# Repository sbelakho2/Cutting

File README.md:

# STARZ Electronics · precision wire cutting and stripping

## Current work: S1-B — fabrication-ready design package (internal build)

**Start building now:** [fabrication guide](docs/31-fabrication-guide.md) —
ordered procurement, machining, assembly, energisation and first-article
steps with every check named. Evidence rules and warnings:
[master plan](docs/24-production-and-release-plan.md). One-page buying list
with every verified price and clickable source:
[sourcing list](docs/32-sourcing-list.md).

- [Selected cutting-axis hardware and scope](engineering/README.md)
- [Manufacturer drawings, actual ratings and rejected mismatches](engineering/sources/catalogue-evidence.md)
- [Shared mechanical/control definition](shared/cutting_head_spec.hpp)
- [Selected-head 3D assembly](engineering/generated/head/head-assembly.step)
- [Part manifest](engineering/generated/head/manifest.csv) and [CAD validation scope](engineering/generated/head/status.json)
- [Dimensioned R6 adapter A3 PDF](engineering/generated/drawings/H003-R6-adapter.pdf) and [browser drawing review](engineering/generated/drawings/index.html)
- [F101 R6 shaft A3 dimension sheet](engineering/generated/drawings/F101-R6-shaft.pdf), [machining-detail sheet](engineering/generated/drawings/F101-R6-details.pdf) and [shaft drawing review](engineering/generated/drawings/shaft-review.html)
- [F101 selected tapping tool and physical-tip setup](docs/14-f101-tapping-operation.md), [fabrication-tooling BOM](bom/fabrication-tooling.csv) and [blank shaft inspection record](docs/inspection/F101-R6.csv)
- [M201 measuring-encoder plate A3 drawing](engineering/generated/drawings/M201-R2-encoder-plate.pdf), [five-part encoder mount STEP](engineering/generated/measurement/encoder-mount.step) and [measurement assembly/calibration record](docs/13-measuring-interfaces-and-calibration.md)
- [P002 payoff spindle A3 drawing](engineering/generated/drawings/P002-R2-payoff-spindle.pdf), [P004–P007 payoff plates A3 drawing](engineering/generated/drawings/P004-P007-R2-payoff-plates.pdf) and [G101–G106 guard panels A3 drawing](engineering/generated/drawings/G101-G106-R2-guard-panels.pdf) with browser reviews (`payoff-spindle-review.html`, `payoff-plates-review.html`, `guard-panels-review.html` in the same directory)
- [Feed cartridge STEP](engineering/generated/feed/feed-cartridge.step), [four-roller layout STEP](engineering/generated/feed-cassette/feed-cassette.step), [machining and assembly record](docs/12-feed-cartridge-fabrication.md), [shaft/belt calculations](engineering/generated/feed-analysis/report.md)
- [Combined head/eight-roller placement STEP](engineering/generated/layout/head-and-feed-layout.step) and [cross-subsystem verification](engineering/generated/layout/status.json)
- [507-occurrence R3 full-machine STEP](engineering/generated/mechanism/full-machine.step) with pressure carriers, wire guides, measuring module, bed, welded frame, R2 guard selections and R2 payoff (spool, spindle, 6204 pockets, brake disc/caliper); [manifest](engineering/generated/mechanism/manifest.csv), [mechanism BOM](engineering/generated/mechanism/mechanism-bom.csv), [scope](engineering/generated/mechanism/status.json); [selected hardware](bom/selected-mechanism.csv) and [custom parts](bom/mechanism-custom-parts.csv)
- [Precision finishing cards](docs/21-precision-finishing.md): per-shaft matched j5 seat grinding and housing fine-boring cards from measured bearing bores
- [Physical qualification procedure and tool](docs/20-physical-qualification.md): ±(0.05 % + 0.20 mm) length cells, nip/wheel force windows, Cpk ≥ 1.33, fail-closed
- [Matched j5/C3 bearing fit](engineering/generated/bearing-fit/report.md) and [shaft matching limits](engineering/generated/bearing-fit/matching-limits.csv)
- [Feed R6 machined-section stiffness audit](engineering/generated/feed-sections/report.md):191 nominal B-rep sections, including the new chamfers and washer/key blends
- [Feed-shaft four-mesh 3D stress study](engineering/generated/feed-fem/report.md) and [model equations](docs/15-feed-shaft-stress-model.md); [torus-root rerun](docs/26-feed-shaft-torus-root-rerun.md); [regional submodel study](docs/28-feed-shaft-submodel-record.md)
- [Earlier focused full-shaft refinements](docs/16-local-shaft-refinement.md): six feature families,26 meshes,three background checks and52 audited fields
- [Earlier CAD-feature refinement and peak audit](docs/17-cad-feature-shaft-refinement.md)
- [Current A12 boundary-topology and stress investigation](docs/18-a12-boundary-topology.md)
- [Exterior-centroid diagnosis and torus-focused resolution](docs/19-exterior-centroid-diagnosis.md)
- [Current design basis and process geometry](docs/01-design-basis.md)
- [Current analytic-only report](engineering/generated/current-analytical/report.md) and [current numerical checks](engineering/generated/current-analytical/checks.csv); [archived R4 full FEM report](engineering/generated/analysis/report.md) and [historical sensitivity studies](engineering/generated/analysis/sensitivity.csv)
- [Adapter FEM with the preloaded elastic-foundation support](engineering/generated/adapter-r6-analysis/report.md)
- [Measuring-wheel calculation and calibration report](engineering/generated/measurement-analysis/report.md)
- [Production controller source](software/machine/): host-testable sequencing core, Pico 2/RP2350 target source and USB commissioning CLI
- [Legacy reference controls](software/firmware/firmware_controller.cpp): retained fault-injection model; does not operate hardware
- [IF-B01 placed/routed draft and manufacturing outputs](hardware/if-b01/README.md)
- [Cabinet controls and wiring design input](docs/22-controls-and-wiring.md)
- [Preliminary guard/payoff CAD accommodation](docs/25-preliminary-guard-and-payoff.md)
- [Guard/payoff R2 selection record](docs/26-guard-and-payoff-selection.md)
- [Machine assembly sequence and interface-fit register](docs/30-machine-assembly-sequence.md)
- [Physical contradiction audit](docs/28-physical-contradiction-audit.md)
- [Gate ledger — every open gate, category and closure action](docs/33-gate-ledger.md)
- [Purchase enquiries — ready-to-send letters for every external line](docs/35-purchase-enquiries.md)
- [Commissioning runbook — 11 phases, 69 steps closing every physical gate](docs/36-commissioning-runbook.md)
- [Weld and assembly procedures (payoff and guard)](docs/34-weld-and-assembly-procedures.md)
- [Master production and release plan](docs/24-production-and-release-plan.md): stepwise procurement, fabrication, assembly, inspection, commissioning and first-article gates; templates remain blank until actual work is performed.
- [Auditable sourcing evidence](bom/sourcing-evidence.csv): direct public-page observations and exact-SKU comparison boundaries; no delivered-cost claim without equivalent quotations. Added 2026-09-13: LC1D12BD EUR70.40 (Automation24), SKF bearing/retention GBP prices (Simply Bearings), with FAG/KOYO quality-equivalent comparisons in [catalogue evidence](engineering/sources/catalogue-evidence.md).
- [IF-B01/RP2350 GPIO allocation](hardware/if-b01/if-b01-gpio-allocation.csv): machine-readable connector-to-firmware allocation checked against the native intent, cabinet schedule and RP2350 source.

The new cutting head uses two complete HIWIN KK8610C-340A1-F0 axes (C-grade substitution, priced on the MISUMI VN shelf 2026-09-16) with real10mm lead, two34E1K-85/CL86T-V41 motor/driver kits and R+W MK2/100/50/8/14 couplings. The motors use original supplier STEP geometry, including cables and connectors, with the supplied removable shaft key removed for the keyless hub. Other purchased head components use catalogue-interface geometry.

The measuring-wheel source audit corrected the free circumference tolerance to **100±0.1 mm** and the uncalibrated1m allocation sum to **1.65 mm**, above the0.70 mm target. The new C++ phase-map fitter checks signed counts, reversals, observable data and independent validation residuals; its example data are **synthetic**, not measured calibration. The encoder tip is20 mm from its mounting face. The full-machine source includes the measuring shaft, pressure carriers and wire guides; each remains unbuilt and unqualified. The287-part combined head/feed layout is unchanged.

## Reproducibility

C++20; CMake/Ninja; OpenCASCADE7.9.3; Eigen; Gmsh; SuiteSparse/CHOLMOD with METIS. The `engineering` CMake preset builds the current head and numerical verification. The `engineering_generate` build target writes CAD/readback artifacts and engineering reports. The root `core` and `sanitize` presets build/test the host-side machine core and retained legacy reference code; `sanitize` enables AddressSanitizer and UndefinedBehaviorSanitizer. Root CTest also executes Python source-record validators for production evidence, IF-B01/RP2350 allocation and published mechanism artifacts; the C++ replacement engineering suite itself has no Python runtime dependency. When a compiler or cache option changes, configure with `cmake --fresh --preset <name>` so preset values are fully reapplied. The separate Pico SDK project under `software/machine/rp2350` builds target UF2 images. No build is physical qualification or permission to energise equipment.

The current **head R6 / feed R6 / measuring R1 / mechanism R3** source state extends the prior 492-part R1 mechanism to 507 source occurrences: eight R2-selected guard/actuator solids and seven R2 payoff solids (welded spool, Ø20 spindle, two 6204-pocket posts, base, brake disc, caliper bracket). Its mechanism test set covers the two wire diameters, STEP export/readback and four rejection cases (shifted bushing, slack carrier spring, light wheel and blocked guard wire route). Historical verification records for the earlier source states (64/64, 52/52, 54/54 native and ASan/UBSan runs, A12 topology, exterior-centroid diagnosis) are preserved in [docs/verification/](docs/verification/). The torus-root rerun ([record](docs/26-feed-shaft-torus-root-rerun.md)) and the [regional submodel study](docs/28-feed-shaft-submodel-record.md) close the feed-shaft regional gates; the adapter FEM now uses a preloaded Winkler elastic-foundation support ([report](engineering/generated/adapter-r6-analysis/report.md)). **The engineering suite is 83/83 native tests passing in 1847.54 s** at this source state; the core and sanitize presets pass 18/18 each.

Head:55 occurrences; cartridge32; four-roller layout116; combined head/eight-roller placement287; separate encoder face mount8. Head/feed moving parts retain17.5 mm X separation for all independent jawY positions. Feed report:25 checks,0 failures; nominal machined-section audit:191 sections,0 sampled stiffness failures. Bearing fit:256 corners,minimum1.28 µm residual clearance **conditional on its declared thermal envelope**,not a measured temperature prediction. Measurement report:392 synthetic held-out observations,0 residual failures; factory accuracy and the626 CN thermal screen remain open. Tests verify their declared software/model scope,not physical machine certification.

## Repository contents (cleaned 2026-09-13)

Every remaining file is a deliverable or its evidence. Build trees are not kept; regenerate with the presets below.

| Path | Content |
|---|---|
| [shared/](shared/) | Frozen C++ specifications: cutting head, feed drive, measurement, machine limits |
| [engineering/](engineering/README.md) | C++20 CAD generators, FEM/fit/calibration models, mechanism integration, finishing and qualification tools, 81 currently configured CTest regressions, vendor originals ([sources/](engineering/sources/catalogue-evidence.md)), public STEP/STL/PDF/CSV outputs and all numerical study records ([generated/](engineering/generated/)) |
| [docs/](docs/01-design-basis.md) | Design basis, Komax benchmark, fabrication/assembly/inspection/calibration records, stress-study records and [verification records](docs/verification/) |
| [bom/](bom/README.md) | Active mechanical and controls selections, custom parts and fabrication tooling; only limited mechanical subtotals are calculated and no delivered machine/cabinet cost exists |
| [software/](software/README.md) | Legacy reference controller and Qt monitor, host-testable production-controller core, Pico 2/RP2350 source and USB commissioning CLI; none is physically qualified |
| [tools/capture_vendor_documents.cpp](tools/capture_vendor_documents.cpp) | Local-only receiver used to archive supplier documents; no network client |
| [branding/](branding/README.md), [brand-board.jpg](branding/brand-board.jpg) | Brand board and approximate trace |

Superseded S1-A CAD, withdrawn BOM/cost/physics/software-architecture documents, duplicate downloads and the final CTest logs are archived outside the repository as `Cutting-superseded-2026-09-13.tar.zst` and are not authority for anything.

## Manufacturability and cost

- Custom metal parts are limited to H001/H002/H003/H004, F101–F112, M201, the guard G101–G106 and payoff P001–P007 parts; all are prismatic, turned or welded-laser parts for the available laser/brake/CNC, with dimensioned A3 sheets for H003, F101, M201, P002, P004–P007 and G101–G106. F101 bearing seats (12/15 j5 matched to measured bores, cylindricity1 µm, Ra0.4 µm) and the blade seat require outsourced grinding.
- Purchased parts are catalogue items from HIWIN, STEPPERONLINE, R+W, MISUMI, SKF, SEEGER, Kübler, Autonics, Rittal and the documented controls suppliers. Observed prices and quotation requests: [sourcing evidence](bom/sourcing-evidence.csv) and [master plan §2](docs/24-production-and-release-plan.md).
- Komax's published length repeatability is ±(0.2%+1 mm); the S1 target ±(0.20 mm+0.05%) is tighter on paper and **unmeasured**; see [the benchmark](docs/02-benchmarks-and-sources.md).

## Warnings (consolidated)

- Fabrication may start now (internal build). Energisation and commissioning are gated: all `physical_results`, `fabrication_released` and `full_machine_integrated` flags remain false until the machine is built and measured.
- Physical measurements that block first use — matched bearing fits, torque/preload records, weld inspection, spring-force settings, blade edge qualification, stop-time and bus-decay, risk-assessment sign-off, full-spool weighing, Cpk runs — have defined procedures and blank templates and cannot be closed on a desk.
- Simulation state: the adapter raw-peak gate is REFINE (pressure-patch edge; contact analysis with measured joint stiffness pending); the 34-exterior centroid whole-shaft audit and preload/contact/fatigue/thermal qualifications remain held; no FEM number releases a part.
- Electrical: the LC1D12BD DC switching duty answer is outstanding; the XPS fuse is DF2CN2 (2 A); cabinet energisation is prohibited until the docs/22 holds have evidence.
- Guard: the 30 mm apertures pass the desk reach calculation but require risk-assessment sign-off; full-spool mass ≤30 kg until the spindle deflection re-check.

## Brand and fabrication

[Original brand artwork](branding/brand-board.jpg); [approximate SVG trace and limitations](branding/README.md). Custom load-bearing parts are metal; the Bambu printer is for noncritical guides/covers. Availability of a CNC or laser is not evidence of grinding-level accuracy, heat-treatment capability or machine safety compliance.

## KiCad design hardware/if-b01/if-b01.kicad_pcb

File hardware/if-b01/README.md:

# IF-B01 control interface board — placed/routed draft source

**Status: a complete native KiCad 10 source and a source-generated draft output
package exist, but neither is released for fabrication, assembly, energisation
or machine operation.** The current four-layer, $750\times400\ \mathrm{mm}$
board source contains every electrical footprint and routing. KiCad 10.0.6
reports zero ERC violations, zero physical DRC violations, zero unconnected
pads and zero schematic-parity issues. The source-generated Gerber, drill,
placement, board-only STEP, IPC-D-356 and BOM files are available as an
explicitly marked draft package.

These source checks demonstrate only consistency of the controlled KiCad
files. They do not approve the deliberately spacious routing-cell layout,
component land patterns, connector fit, panel size, stack-up, electrical
design, fabrication, assembled board, cabinet integration or safety function.

IF-B01 is intended to be the PELV/SELV interface between a Raspberry Pi Pico 2
and 24 V common-anode drive inputs, indicators, dry-contact field interfaces,
and 5 V single-ended TTL measuring encoders (ifm RU3100 parameterised to TTL
mode). It contains neither mains circuitry nor a
functional-safety circuit. The XPS relay, E-stop, guard contacts and contactors
remain hardwired cabinet functions described as an unreleased design concept in
[the cabinet control record](../../docs/22-controls-and-wiring.md).

## Current design intent

| Function | Draft implementation | Controller-facing result |
|---|---|---|
| PUL/DIR | `TPL7407LDR` low-side NMOS channels to common-anode 24 V inputs | `GP0`–`GP7` high is intended to sink the named drive input |
| Shared enable | One `TPL7407LDR` channel with a `100 kΩ` input pull-down | `GP17` high is intended to sink every `ENA−`; reset/power loss should keep the channel off |
| Indicator/buzzer | `TPL7407LDR` low-side channels | `GP22`, `GP26`, `GP28` high are intended to sink the assigned 24 V load |
| Measuring encoders | `AM26LV32EIDR` 3.3 V receiver (input common mode −7…+7 V); the RU3100 single-ended TTL A/B drive the `+` inputs directly and each `−` input carries an on-board 2.5 V mid-bias (R38–R45 10 kΩ 1 %, C14–C17 100 nF); the former R1–R4 120 Ω terminators are removed | Non-inverted A/B outputs intended for `GP8`–`GP11` |
| Field/alarm contacts | Ten protected dry-contact-to-0 V inputs, active low | `GP12`–`GP16`, `GP18`–`GP21` |
| Encoder power | Two individually resettable 5 V branches | One branch per ifm RU3100 encoder |

The firmware-facing signal names and polarities are defined in the
[controls specification](../../shared/controls_spec.hpp). The exact draft
connector-to-net mapping is in [if-b01-netlist.csv](if-b01-netlist.csv), and
the machine-readable cross-check is [if-b01-gpio-allocation.csv](if-b01-gpio-allocation.csv).
The allocation checker [check_if_b01_gpio_mapping.py](../../tools/check_if_b01_gpio_mapping.py)
reconciles the board connector CSV, native intent, controller pin constants,
cabinet relay schedule and RP2350 PIO setup. A label, connector position,
library symbol or historical board description must not be treated as a
substitute for a reviewed native schematic.

## Native-draft files presently available

| File | Meaning | What it is not |
|---|---|---|
| [if-b01.kicad_pro](if-b01.kicad_pro) | KiCad 10 project entry point | A board release |
| [if-b01.kicad_sch](if-b01.kicad_sch) | Editable logical schematic with embedded exact local symbols | A completed electrical design review |
| [if-b01.kicad_sym](if-b01.kicad_sym) / [if-b01.pretty](if-b01.pretty) | Project-local draft symbol and footprint libraries | Checked component land-pattern approval |
| [if-b01.kicad_pcb](if-b01.kicad_pcb) | Editable four-layer $750\times400\ \mathrm{mm}$ placed/routed draft PCB, including all board footprints, copper and four M3 holes | A released or fabrication-approved layout |
| [if-b01-native-intent.json](if-b01-native-intent.json) | Generated BOM, pin/net and release-hold manifest | A fabrication bill of materials |
| [review/if-b01-native-source-review.md](review/if-b01-native-source-review.md) | Interpretation of recorded source-level KiCad checks | A design-review approval or release record |
| [review/if-b01-erc.rpt](review/if-b01-erc.rpt) | KiCad 10.0.6 ERC result: zero reported violations | Human electrical review or qualification evidence |
| [review/if-b01-netlist.net](review/if-b01-netlist.net) / [review/if-b01-native-bom.csv](review/if-b01-native-bom.csv) | Native KiCad export evidence compared with the manifest | A released manufacturing export |
| [review/if-b01-pcb-drc.rpt](review/if-b01-pcb-drc.rpt) | KiCad 10.0.6 physical plus schematic-parity result: zero DRC violations, zero unconnected pads and zero parity issues | A human design review, fabrication approval or qualification result |
| [review/if-b01-pcb-prelayout-drc.rpt](review/if-b01-pcb-prelayout-drc.rpt) | Historical pre-layout record retained for traceability | The result for the current board |
| [if-b01-netlist.csv](if-b01-netlist.csv) | Intended connector, net and firmware-signal mapping | A netlist generated and checked by an EDA system |
| [if-b01-bom.csv](if-b01-bom.csv) | Intended electrical parts, packages and connector identities | A placed, approved or fabrication BOM |
| [if-b01-placement.csv](if-b01-placement.csv) | Generator-owned exact footprint coordinate schedule for the current board | An approved assembly instruction |
| [if-b01-assembly.md](if-b01-assembly.md) | Draft assembly/inspection procedure tied to current source outputs | A released work instruction |
| [if-b01-test.md](if-b01-test.md) | Fixture-only board test procedure | A production-machine commissioning procedure |
| [if-b01-cabinet-integration.md](if-b01-cabinet-integration.md) | Cabinet terminal, relay-contact, encoder and indication integration schedule | A cabinet wiring release or safety circuit |

| [manufacturing/draft-r2-2026-09-13](manufacturing/draft-r2-2026-09-13) | Verification-gated draft Gerber, drill, placement, visual assembly, board-only STEP, IPC-D-356, BOM and SHA-256 manifest package | A release package or authorisation to order/build |

The deterministic generator [generate_if_b01_kicad.py](../../tools/generate_if_b01_kicad.py)
reconciles the input BOM, connector allocation and fixed IC channels before it
writes the native source. The parity check
[check_if_b01_kicad.py](../../tools/check_if_b01_kicad.py) checks the actual
KiCad netlist and BOM exports: 112 BOM references, 102 electrically represented
netlist references, 298 connected symbol pins and six deliberate no-connects.
The allocation check [check_if_b01_gpio_mapping.py](../../tools/check_if_b01_gpio_mapping.py)
additionally recomputes the physical Pico 2 pin of every J1/J2 pad from its PCB
coordinates and fails on a reversed or mirrored socket row, and verifies the
dry-contact pull-configuration contract. The
[output generator](../../tools/export_if_b01_manufacturing.py) refuses stale
source or any ERC/DRC/parity violation before it writes the draft package. These
checks constrain transcription and layout errors; they do not replace
electrical, mechanical, PCB, fabrication or safety review.

## Fixed electrical allocation to preserve in schematic capture

| Array | Intended channel assignment |
|---|---|
| U2 `TPL7407LDR` | BF `PUL−`, BF `DIR−`, BR `PUL−`, BR `DIR−`, FL `PUL−`, FL `DIR−`, FR `PUL−` |
| U3 `TPL7407LDR` | FR `DIR−`, shared `ENA−`, green LED negative, red LED negative, buzzer negative |
| U3 unused channels | Inputs tied low; no field connection permitted |
| U1 `AM26LV32EIDR` | Left A, left B, right A, right B; only non-inverted receiver outputs go to the Pico |

The U2/U3 low-side outputs connect only to the named negative drive/load
terminals. The corresponding PUL/DIR/ENA positives are separately protected
`+24V_DRVLOGIC` cabinet wiring and must not be routed through IF-B01. The
IF-B01 `0V_PELV` pins are references/test returns, not a substitute for the
selected driver input wiring.

## Connector and protection intent

The currently named Phoenix Contact MSTB 5.08 mm headers and matching plugs in
[if-b01-bom.csv](if-b01-bom.csv) are draft selections. Exact fit, creepage,
clearance, conductor range, mating orientation, current capacity, availability
and assembly compatibility require schematic/PCB review.

| Ref | Positions | Draft function |
|---|---:|---|
| J1/J2 | 20 + 20 | Pico 2 socket rows |
| J3 | 4 | `+24V_PELV`, `0V_PELV`, `+5V_LOGIC`, `0V_PELV` |
| J4–J7 | 4 each | BF, BR, FL, FR: `PUL−`, `DIR−`, `ENA−`, `0V_PELV` |
| J8/J9 | 6 each | Left/right ifm RU3100 encoder: `+5V`, `0V`, `A+`, `A−`, `B+`, `B−` (single-ended A/B to the + terminals; the − terminals are the on-board 2.5 V receiver mid-bias nodes, not encoder wires) |
| J10 | 12 | Six isolated field-input contact pairs |
| J11 | 8 | Four isolated driver-alarm contact pairs |
| J12 | 4 | `GREEN−`, `RED−`, `BUZZER−`, `0V_PELV` |

Each planned dry-contact input has a 10 kΩ series resistor, 47 kΩ 1 % pull-up,
10 nF filter and 3.6 V clamp on the board side. An isolated NO contact is
intended to close `SIG` to `0V_PELV`, producing a low asserted level. Because the
10 kΩ series resistor sits between the field terminal and the 47 kΩ board
pull-up, the RP2350 internal pull-up must be **disabled** on all ten input GPIOs
(`GP12`–`GP16`, `GP27`, `GP18`–`GP21`) in both firmware images; with the internal
pull enabled the asserted LOW can reach 0.82–1.14 V and exceed the RP2350
`VIL(max)` of 0.8 V. The board-only network guarantees
`0.579 V = 3.3 V × 10 kΩ / (10 kΩ + 47 kΩ)` at the pin. The generated schematic
carries the same pull-configuration contract and
`tools/check_if_b01_gpio_mapping.py` verifies the contract list. Each encoder
supply branch and the TPL `COM` feed pass through verified 1812 SMD PTCs:
F1 `MF-MSMF050/60X` (60 V, 24 V branch) and F2/F3 `MF-MSMF050/16X` (16 V, 5 V
encoder branches), both 0.50 A hold, per the Bourns MF-MSMF datasheet. These
values require schematic/ERC review and physical testing; neither a CSV nor a
firmware pull-up proves their behaviour.

For encoder cables, the intended order is the RU3100 single-ended allocation:
A and B to the J8/J9 A+/B+ terminals; the RU3100 has no A-bar/B-bar outputs,
so the A−/B− terminals are the receiver **mid-bias** nodes, held at 2.5 V by the
on-board R38–R45/C14–C17 network — no A−/B− wire is fitted. Parameterise each
RU3100 to **TTL mode** and **2048 PPR** via IO-Link before wiring (factory
setting is HTL, 1024 PPR); the parameterisation needs an IO-Link master with a
Class A M12 port (see [docs/23](../../docs/23-cabinet-electrical-assembly.md)).
The Z conductor stays unconnected and individually insulated (it doubles
as the IO-Link line for bench parameterisation). Bond the cable screen at the
cabinet PE entry, never to IF-B01 `0V_PELV`.

## Safety boundary

The board's `GP17` pull-down, controller watchdog, firmware safety interrupt,
USB transport and output arrays are supplemental control measures only. They
do not provide safe torque off, contactor isolation, safe discharge, guard
unlock permission or a personnel-safety function. See
[the cabinet control record](../../docs/22-controls-and-wiring.md) for the
proposed hardwired XPS/E-stop/guard/contactors topology and its unresolved
release holds.

## Fixture-only firmware and test boundary

Use the dedicated `if-b01-factory-test.uf2` image only on a bare IF-B01 fixture
with J4–J7 unplugged from production motor drivers. It deliberately has no
production `Controller` or step-motion PIO. It begins with every TPL input low,
requires active-low `SAFETY_OK` plus held active-low `RESET` before output
testing, limits arming to 30 seconds and limits a selected output to three
seconds. The exact procedure and command map are in
[if-b01-test.md](if-b01-test.md).

The production `starz-machine.uf2` image is not an individual-output test
tool. Do not extend it with fixture commands or use the factory image on an
assembled cabinet/machine.

## Local EDA toolchain status

Checked on 2026-09-13: `kicad-cli --version` reports **10.0.6**. The current
logical schematic returns zero KiCad ERC violations; native-netlist/BOM parity
passes against the generated intent manifest; and the routed board returns zero
physical DRC violations, zero unconnected pads and zero schematic-parity
issues. The output-pipeline manifest records SHA-256 values for every source and
draft output. KiCad parsing, ERC, DRC and parity cleanliness are not release
verdicts and must not be presented as a substitute for review or physical
evidence.

## Preconditions for a future board release

1. Complete human electrical and mechanical review of the logical capture and
	current layout, including the $750\times400\ \mathrm{mm}$ panel, actual
	component footprints, connector orientation, Pico socket geometry, protection
	values, TPL COM slew/bulk capacitance, cable use, return paths and stack-up.
2. Obtain fabricator confirmation of panel capability, finished copper/stack-up,
	drill, clearance, mask, silkscreen and assembly process constraints; revise
	the source if any requirement differs from the draft assumptions.
3. Inspect a fabricated bare board and build it only under a reviewed assembly
	process. Run the isolated fixture procedure and record all actual results.
4. Complete cabinet, DC-power, PE, guarding, EMC, safety-function and machine
	qualification evidence before permitting machine energisation.

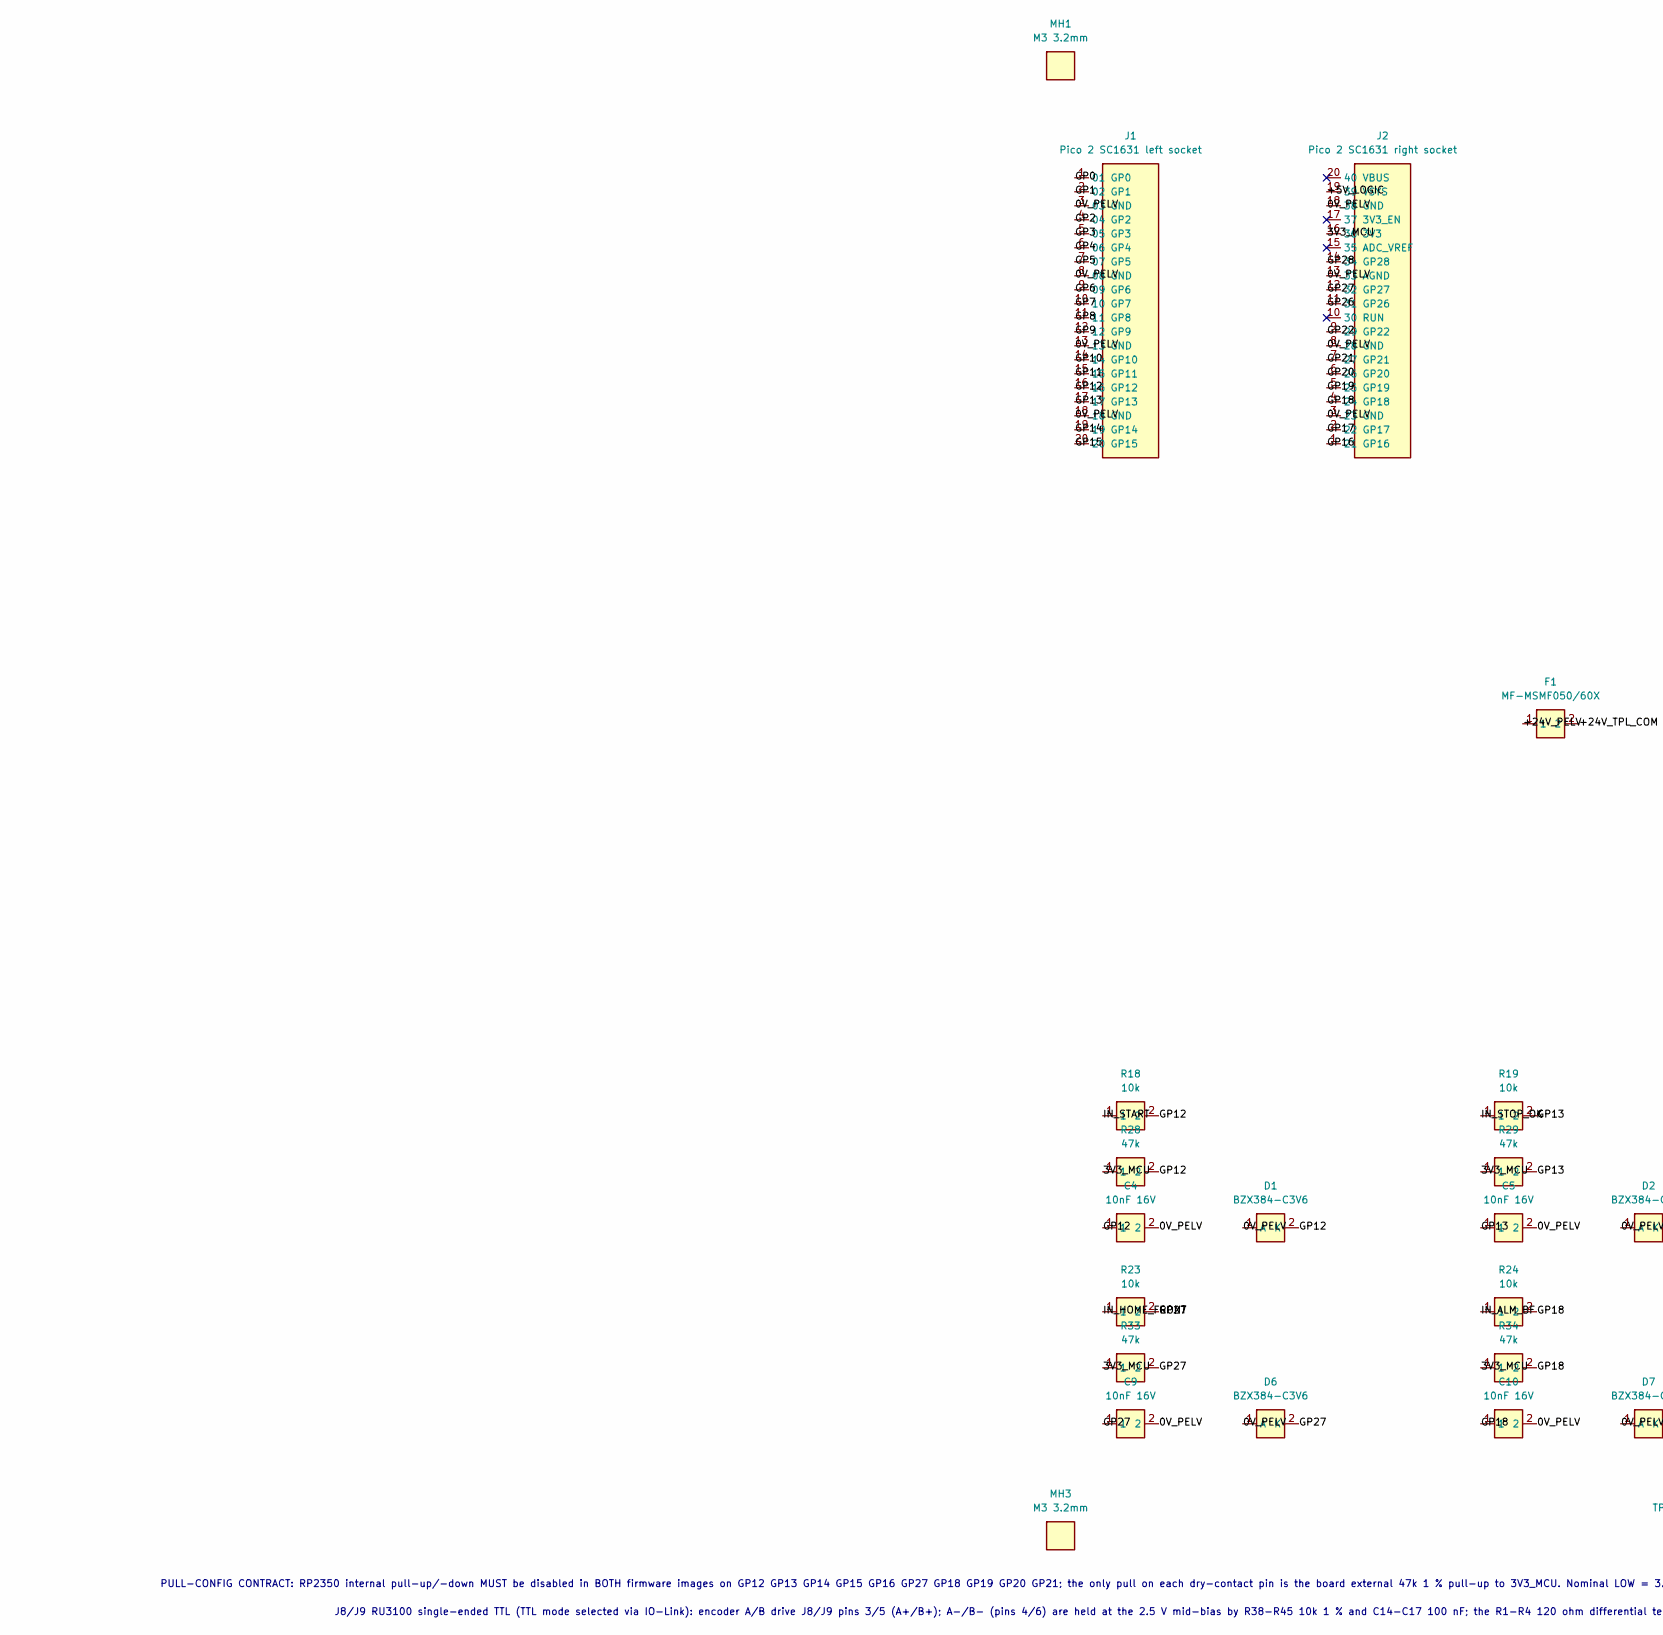
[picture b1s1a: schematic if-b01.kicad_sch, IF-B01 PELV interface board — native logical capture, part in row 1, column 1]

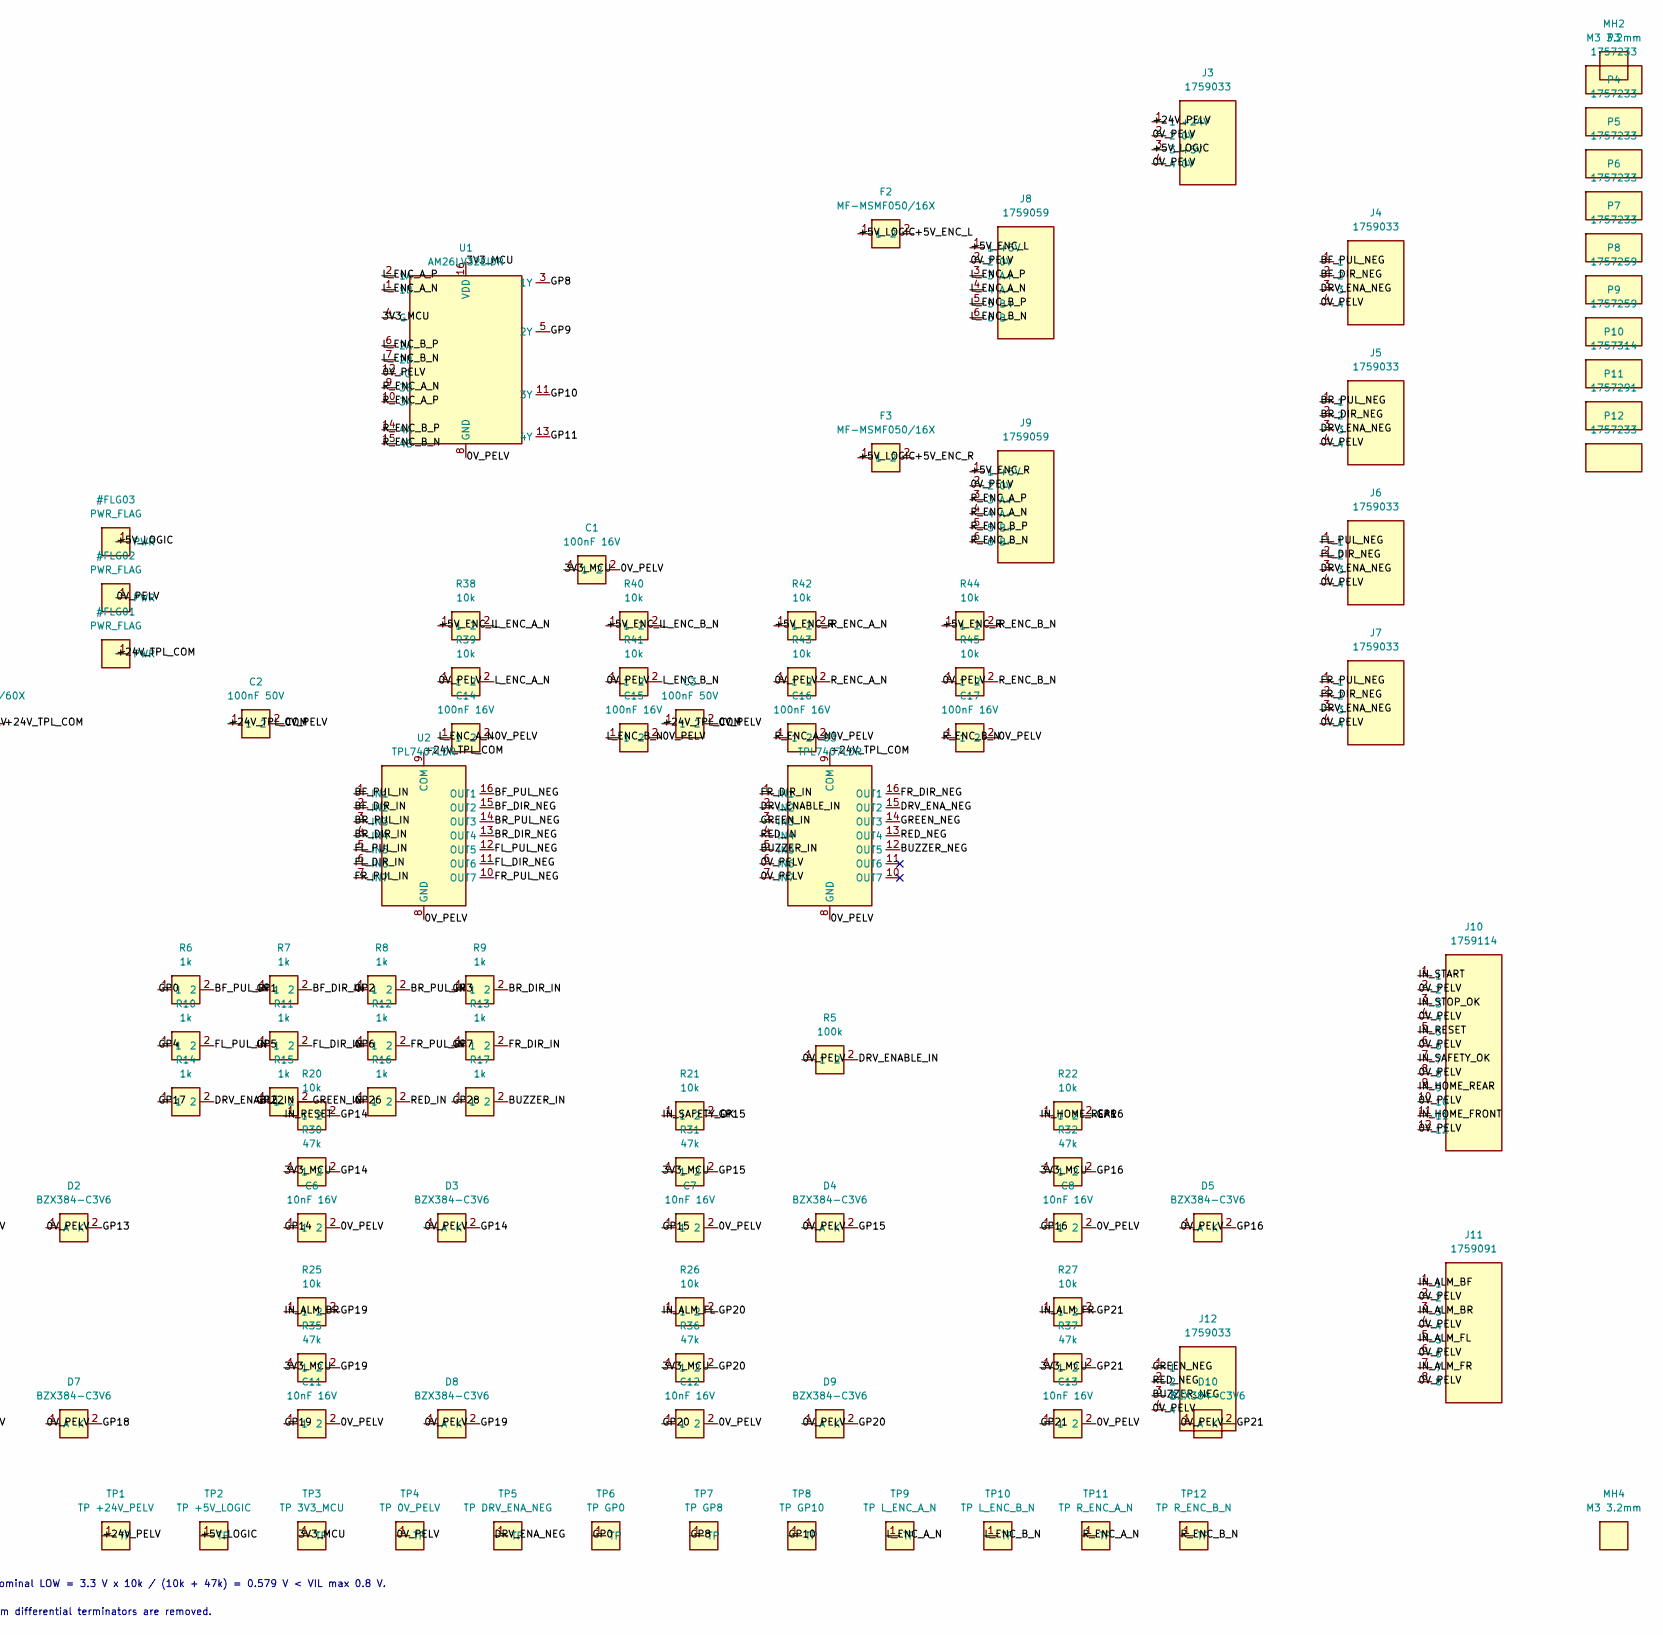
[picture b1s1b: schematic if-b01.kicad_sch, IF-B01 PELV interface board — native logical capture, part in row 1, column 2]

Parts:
C1, C14, C15, C16, C17: 100nF 16V; C_0603_1608; MPN GRM188R71C104KA01D
C2, C3: 100nF 50V; C_0603_1608; MPN GRM188R71H104KA93D
C4, C5, C6, C7, C8, C9, C10, C11, C12, C13: 10nF 16V; C_0603_1608; MPN GRM188R71C103KA01D
D1, D2, D3, D4, D5, D6, D7, D8, D9, D10: BZX384-C3V6; SOD_323; MPN BZX384-C3V6
F1: MF-MSMF050/60X; PTC_1812; MPN MF-MSMF050/60X
F2, F3: MF-MSMF050/16X; PTC_1812; MPN MF-MSMF050/16X
J1: Pico 2 SC1631 left socket; PICO_SOCKET_1X20; MPN SSQ-120-23-G-S
J2: Pico 2 SC1631 right socket; PICO_SOCKET_1X20_RIGHT; MPN SSQ-120-23-G-S
J3, J4, J5, J6, J7, J12: 1759033; MSTB_2_5_4_G_5_08; MPN 1759033
J8, J9: 1759059; MSTB_2_5_6_G_5_08; MPN 1759059
J10: 1759114; MSTB_2_5_12_G_5_08; MPN 1759114
J11: 1759091; MSTB_2_5_8_G_5_08; MPN 1759091
MH1, MH2, MH3, MH4: M3 3.2mm; MountingHole_3_2mm_M3; MPN 9903
P3, P4, P5, P6, P7, P12: 1757233; MPN 1757233
P8, P9: 1757259; MPN 1757259
P10: 1757314; MPN 1757314
P11: 1757291; MPN 1757291
R5: 100k; R_0603_1608; MPN RC0603FR-07100KL
R6, R7, R8, R9, R10, R11, R12, R13, R14, R15, R16, R17: 1k; R_0603_1608; MPN RC0603FR-071KL
R18, R19, R20, R21, R22, R23, R24, R25, R26, R27, R38, R39, R40, R41, R42, R43, R44, R45: 10k; R_0603_1608; MPN RC0603FR-0710KL
R28, R29, R30, R31, R32, R33, R34, R35, R36, R37: 47k; R_0603_1608; MPN RC0603FR-0747KL
TP1: TP +24V_PELV; TestPoint_1_0mm; MPN 5000
TP2: TP +5V_LOGIC; TestPoint_1_0mm; MPN 5000
TP3: TP 3V3_MCU; TestPoint_1_0mm; MPN 5000
TP4: TP 0V_PELV; TestPoint_1_0mm; MPN 5000
TP5: TP DRV_ENA_NEG; TestPoint_1_0mm; MPN 5000
TP6: TP GP0; TestPoint_1_0mm; MPN 5000
TP7: TP GP8; TestPoint_1_0mm; MPN 5000
TP8: TP GP10; TestPoint_1_0mm; MPN 5000
TP9: TP L_ENC_A_N; TestPoint_1_0mm; MPN 5000
TP10: TP L_ENC_B_N; TestPoint_1_0mm; MPN 5000
TP11: TP R_ENC_A_N; TestPoint_1_0mm; MPN 5000
TP12: TP R_ENC_B_N; TestPoint_1_0mm; MPN 5000
U1: AM26LV32EIDR; SOIC_16_3_9x9_9_P1_27; MPN AM26LV32EIDR
U2, U3: TPL7407LDR; SOIC_16_3_9x9_9_P1_27; MPN TPL7407LDR

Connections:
/0V_PELV: C1.2, C2.2, C3.2, C4.2, C5.2, C6.2, C7.2, C8.2, C9.2, C10.2, C11.2, C12.2, C13.2, C14.2, C15.2, C16.2, C17.2, D1.1 (A), D2.1 (A), D3.1 (A), D4.1 (A), D5.1 (A), D6.1 (A), D7.1 (A), D8.1 (A), D9.1 (A), D10.1 (A), J1.3 (03 GND), J1.8 (08 GND), J1.13 (13 GND), J1.18 (18 GND), J2.3 (23 GND), J2.8 (28 GND), J2.13 (33 AGND), J2.18 (38 GND), J3.2 (2 0V), J3.4 (4 0V), J4.4, J5.4, J6.4, J7.4, J8.2 (2 0V), J9.2 (2 0V), J10.2, J10.4, J10.6, J10.8, J10.10, J10.12, J11.2, J11.4, J11.6, J11.8, J12.4, R5.1, R39.1, R41.1, R43.1, R45.1, TP4.1, U1.8 (GND), U1.12 (~G), U2.8 (GND), U3.6 (IN6), U3.7 (IN7), U3.8 (GND)
/3V3_MCU: C1.1, J2.16 (36 3V3), R28.1, R29.1, R30.1, R31.1, R32.1, R33.1, R34.1, R35.1, R36.1, R37.1, TP3.1, U1.4 (G), U1.16 (VDD)
/+5V_ENC_L: F2.2, J8.1 (1 +5V), R38.1, R40.1
/+5V_ENC_R: F3.2, J9.1 (1 +5V), R42.1, R44.1
/+5V_LOGIC: F2.1, F3.1, J2.19 (39 VSYS), J3.3 (3 +5V), TP2.1
/+24V_PELV: F1.1, J3.1 (1 +24V), TP1.1
/+24V_TPL_COM: C2.1, C3.1, F1.2, U2.9 (COM), U3.9 (COM)
/BF_DIR_IN: R7.2, U2.2 (IN2)
/BF_DIR_NEG: J4.2, U2.15 (OUT2)
/BF_PUL_IN: R6.2, U2.1 (IN1)
/BF_PUL_NEG: J4.1, U2.16 (OUT1)
/BR_DIR_IN: R9.2, U2.4 (IN4)
/BR_DIR_NEG: J5.2, U2.13 (OUT4)
/BR_PUL_IN: R8.2, U2.3 (IN3)
/BR_PUL_NEG: J5.1, U2.14 (OUT3)
/BUZZER_IN: R17.2, U3.5 (IN5)
/BUZZER_NEG: J12.3, U3.12 (OUT5)
/DRV_ENABLE_IN: R5.2, R14.2, U3.2 (IN2)
/DRV_ENA_NEG: J4.3, J5.3, J6.3, J7.3, TP5.1, U3.15 (OUT2)
/FL_DIR_IN: R11.2, U2.6 (IN6)
/FL_DIR_NEG: J6.2, U2.11 (OUT6)
/FL_PUL_IN: R10.2, U2.5 (IN5)
/FL_PUL_NEG: J6.1, U2.12 (OUT5)
/FR_DIR_IN: R13.2, U3.1 (IN1)
/FR_DIR_NEG: J7.2, U3.16 (OUT1)
/FR_PUL_IN: R12.2, U2.7 (IN7)
/FR_PUL_NEG: J7.1, U2.10 (OUT7)
/GP0: J1.1 (01 GP0), R6.1, TP6.1
/GP1: J1.2 (02 GP1), R7.1
/GP2: J1.4 (04 GP2), R8.1
/GP3: J1.5 (05 GP3), R9.1
/GP4: J1.6 (06 GP4), R10.1
/GP5: J1.7 (07 GP5), R11.1
/GP6: J1.9 (09 GP6), R12.1
/GP7: J1.10 (10 GP7), R13.1
/GP8: J1.11 (11 GP8), TP7.1, U1.3 (1Y)
/GP9: J1.12 (12 GP9), U1.5 (2Y)
/GP10: J1.14 (14 GP10), TP8.1, U1.11 (3Y)
/GP11: J1.15 (15 GP11), U1.13 (4Y)
/GP12: C4.1, D1.2 (K), J1.16 (16 GP12), R18.2, R28.2
/GP13: C5.1, D2.2 (K), J1.17 (17 GP13), R19.2, R29.2
/GP14: C6.1, D3.2 (K), J1.19 (19 GP14), R20.2, R30.2
/GP15: C7.1, D4.2 (K), J1.20 (20 GP15), R21.2, R31.2
/GP16: C8.1, D5.2 (K), J2.1 (21 GP16), R22.2, R32.2
/GP17: J2.2 (22 GP17), R14.1
/GP18: C10.1, D7.2 (K), J2.4 (24 GP18), R24.2, R34.2
/GP19: C11.1, D8.2 (K), J2.5 (25 GP19), R25.2, R35.2
/GP20: C12.1, D9.2 (K), J2.6 (26 GP20), R26.2, R36.2
/GP21: C13.1, D10.2 (K), J2.7 (27 GP21), R27.2, R37.2
/GP22: J2.9 (29 GP22), R15.1
/GP26: J2.11 (31 GP26), R16.1
/GP27: C9.1, D6.2 (K), J2.12 (32 GP27), R23.2, R33.2
/GP28: J2.14 (34 GP28), R17.1
/GREEN_IN: R15.2, U3.3 (IN3)
/GREEN_NEG: J12.1, U3.14 (OUT3)
/IN_ALM_BF: J11.1, R24.1
/IN_ALM_BR: J11.3, R25.1
/IN_ALM_FL: J11.5, R26.1
/IN_ALM_FR: J11.7, R27.1
/IN_HOME_FRONT: J10.11, R23.1
/IN_HOME_REAR: J10.9, R22.1
/IN_RESET: J10.5, R20.1
/IN_SAFETY_OK: J10.7, R21.1
/IN_START: J10.1, R18.1
/IN_STOP_OK: J10.3, R19.1
/L_ENC_A_N: C14.1, J8.4 (4 A-), R38.2, R39.2, TP9.1, U1.1 (1B)
/L_ENC_A_P: J8.3 (3 A+), U1.2 (1A)
/L_ENC_B_N: C15.1, J8.6 (6 B-), R40.2, R41.2, TP10.1, U1.7 (2B)
/L_ENC_B_P: J8.5 (5 B+), U1.6 (2A)
/RED_IN: R16.2, U3.4 (IN4)
/RED_NEG: J12.2, U3.13 (OUT4)
/R_ENC_A_N: C16.1, J9.4 (4 A-), R42.2, R43.2, TP11.1, U1.9 (3B)
/R_ENC_A_P: J9.3 (3 A+), U1.10 (3A)
/R_ENC_B_N: C17.1, J9.6 (6 B-), R44.2, R45.2, TP12.1, U1.15 (4B)
/R_ENC_B_P: J9.5 (5 B+), U1.14 (4A)

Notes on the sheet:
PULL-CONFIG CONTRACT: RP2350 internal pull-up/-down MUST be disabled in BOTH firmware images on GP12 GP13 GP14 GP15 GP16 GP27 GP18 GP19 GP20 GP21; the only pull on each dry-contact pin is the board external 47k 1 % pull-up to 3V3_MCU. Nominal LOW = 3.3 V x 10k / (10k + 47k) = 0.579 V < VIL max 0.8 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
J8/J9 RU3100 single-ended TTL (TTL mode selected via IO-Link): encoder A/B drive J8/J9 pins 3/5 (A+/B+); A-/B- (pins 4/6) are held at the 2.5 V mid-bias by R38-R45 10k 1 % and C14-C17 100 nF; the R1-R4 120 ohm differential terminators are removed.

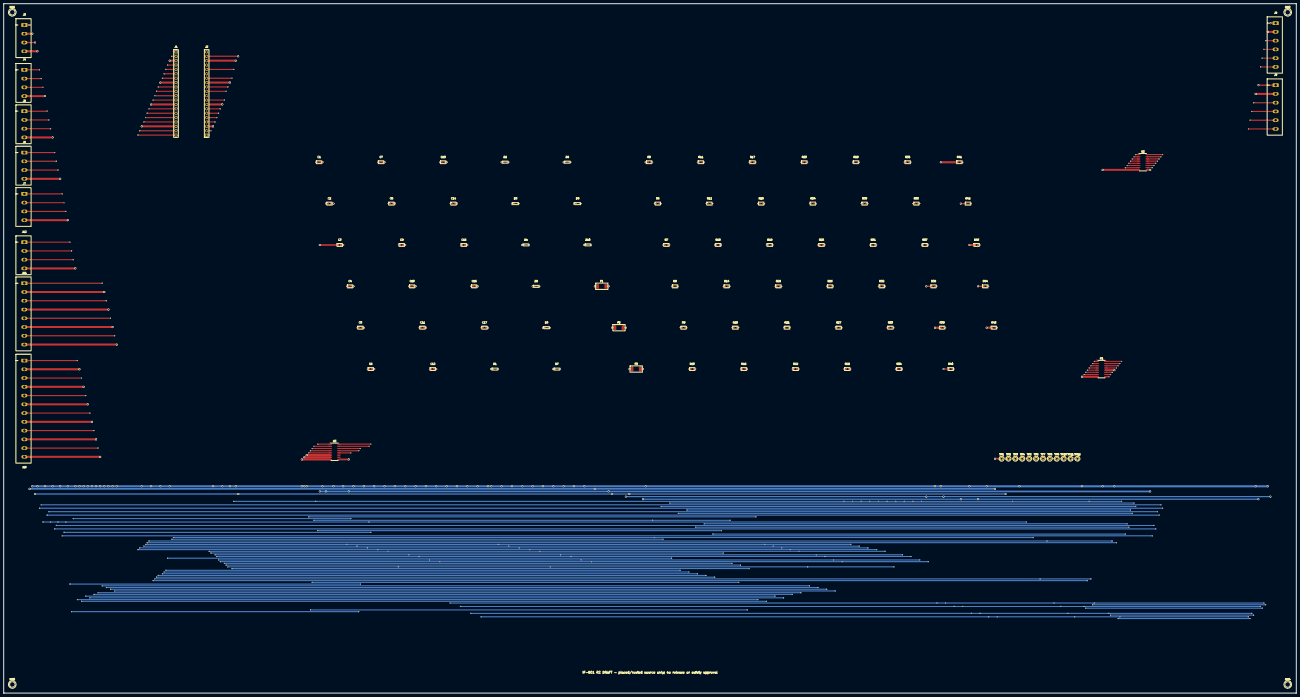
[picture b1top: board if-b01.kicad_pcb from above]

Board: 4 copper layers, 750.0 x 400.0 mm, 102 parts (0 on the bottom side), 75 nets.

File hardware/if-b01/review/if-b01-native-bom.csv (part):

"Reference","Value","Footprint","Manufacturer","MPN","Description","Quantity","DNP"
"C1","100nF 16V","IFB01:C_0603_1608","Murata","GRM188R71C104KA01D","100 nF 16 V X7R ceramic decoupler","1",""
"C2","100nF 50V","IFB01:C_0603_1608","Murata","GRM188R71H104KA93D","100 nF 50 V X7R ceramic bypass capacitor","1",""
"C3","100nF 50V","IFB01:C_0603_1608","Murata","GRM188R71H104KA93D","100 nF 50 V X7R ceramic bypass capacitor","1",""
"C4","10nF 16V","IFB01:C_0603_1608","Murata","GRM188R71C103KA01D","10 nF 16 V X7R input filter","1",""
"C5","10nF 16V","IFB01:C_0603_1608","Murata","GRM188R71C103KA01D","10 nF 16 V X7R input filter","1",""
"C6","10nF 16V","IFB01:C_0603_1608","Murata","GRM188R71C103KA01D","10 nF 16 V X7R input filter","1",""
"C7","10nF 16V","IFB01:C_0603_1608","Murata","GRM188R71C103KA01D","10 nF 16 V X7R input filter","1",""
"C8","10nF 16V","IFB01:C_0603_1608","Murata","GRM188R71C103KA01D","10 nF 16 V X7R input filter","1",""
"C9","10nF 16V","IFB01:C_0603_1608","Murata","GRM188R71C103KA01D","10 nF 16 V X7R input filter","1",""
"C10","10nF 16V","IFB01:C_0603_1608","Murata","GRM188R71C103KA01D","10 nF 16 V X7R input filter","1",""
"C11","10nF 16V","IFB01:C_0603_1608","Murata","GRM188R71C103KA01D","10 nF 16 V X7R input filter","1",""
"C12","10nF 16V","IFB01:C_0603_1608","Murata","GRM188R71C103KA01D","10 nF 16 V X7R input filter","1",""
"C13","10nF 16V","IFB01:C_0603_1608","Murata","GRM188R71C103KA01D","10 nF 16 V X7R input filter","1",""
"C14","100nF 16V","IFB01:C_0603_1608","Murata","GRM188R71C104KA01D","100 nF 16 V X7R bias filter","1",""
"C15","100nF 16V","IFB01:C_0603_1608","Murata","GRM188R71C104KA01D","100 nF 16 V X7R bias filter","1",""
"C16","100nF 16V","IFB01:C_0603_1608","Murata","GRM188R71C104KA01D","100 nF 16 V X7R bias filter","1",""
"C17","100nF 16V","IFB01:C_0603_1608","Murata","GRM188R71C104KA01D","100 nF 16 V X7R bias filter","1",""
"D1","BZX384-C3V6","IFB01:SOD_323","Nexperia","BZX384-C3V6","3.6 V input clamp diode","1",""
"D2","BZX384-C3V6","IFB01:SOD_323","Nexperia","BZX384-C3V6","3.6 V input clamp diode","1",""
"D3","BZX384-C3V6","IFB01:SOD_323","Nexperia","BZX384-C3V6","3.6 V input clamp diode","1",""
"D4","BZX384-C3V6","IFB01:SOD_323","Nexperia","BZX384-C3V6","3.6 V input clamp diode","1",""
"D5","BZX384-C3V6","IFB01:SOD_323","Nexperia","BZX384-C3V6","3.6 V input clamp diode","1",""
"D6","BZX384-C3V6","IFB01:SOD_323","Nexperia","BZX384-C3V6","3.6 V input clamp diode","1",""
"D7","BZX384-C3V6","IFB01:SOD_323","Nexperia","BZX384-C3V6","3.6 V input clamp diode","1",""
"D8","BZX384-C3V6","IFB01:SOD_323","Nexperia","BZX384-C3V6","3.6 V input clamp diode","1",""
"D9","BZX384-C3V6","IFB01:SOD_323","Nexperia","BZX384-C3V6","3.6 V input clamp diode","1",""
"D10","BZX384-C3V6","IFB01:SOD_323","Nexperia","BZX384-C3V6","3.6 V input clamp diode","1",""
"F1","MF-MSMF050/60X","IFB01:PTC_1812","Bourns","MF-MSMF050/60X","0.50 A hold 60 V 1812 SMD resettable PTC; +24V_TPL_COM branch; pads per the Bourns recommended layout (1.68 x 2.95 mm, 3.1 mm gap)","1",""
"F2","MF-MSMF050/16X","IFB01:PTC_1812","Bourns","MF-MSMF050/16X","0.50 A hold 16 V 1812 SMD resettable PTC; one per encoder 5 V branch; pads per the Bourns recommended layout (1.68 x 2.95 mm, 3.1 mm gap)","1",""
"F3","MF-MSMF050/16X","IFB01:PTC_1812","Bourns","MF-MSMF050/16X","0.50 A hold 16 V 1812 SMD resettable PTC; one per encoder 5 V branch; pads per the Bourns recommended layout (1.68 x 2.95 mm, 3.1 mm gap)","1",""
"J1","Pico 2 SC1631 left socket","IFB01:PICO_SOCKET_1X20","Samtec","SSQ-120-23-G-S","Pico 2 left socket row","1",""
"J2","Pico 2 SC1631 right socket","IFB01:PICO_SOCKET_1X20_RIGHT","Samtec","SSQ-120-23-G-S","Pico 2 right socket row","1",""
"J3","1759033","IFB01:MSTB_2_5_4_G_5_08","Phoenix Contact","1759033","4-position 5.08 mm PCB plug header","1",""
"J4","1759033","IFB01:MSTB_2_5_4_G_5_08","Phoenix Contact","1759033","blade-front drive 4-position PCB plug header","1",""
"J5","1759033","IFB01:MSTB_2_5_4_G_5_08","Phoenix Contact","1759033","blade-rear drive 4-position PCB plug header","1",""
"J6","1759033","IFB01:MSTB_2_5_4_G_5_08","Phoenix Contact","1759033","feed-left drive 4-position PCB plug header","1",""
"J7","1759033","IFB01:MSTB_2_5_4_G_5_08","Phoenix Contact","1759033","feed-right drive 4-position PCB plug header","1",""
"J8","1759059","IFB01:MSTB_2_5_6_G_5_08","Phoenix Contact","1759059","left encoder 6-position PCB plug header","1",""
"J9","1759059","IFB01:MSTB_2_5_6_G_5_08","Phoenix Contact","1759059","right encoder 6-position PCB plug header","1",""
"J10","1759114","IFB01:MSTB_2_5_12_G_5_08","Phoenix Contact","1759114","field-contact 12-position PCB plug header","1",""
"J11","1759091","IFB01:MSTB_2_5_8_G_5_08","Phoenix Contact","1759091","drive-alarm 8-position PCB plug header","1",""
"J12","1759033","IFB01:MSTB_2_5_4_G_5_08","Phoenix Contact","1759033","indicator and buzzer 4-position PCB plug header","1",""
"MH1","M3 3.2mm","IFB01:MountingHole_3_2mm_M3","Keystone","9903","M3 nylon board mounting hardware set","1",""
"MH2","M3 3.2mm","IFB01:MountingHole_3_2mm_M3","Keystone","9903","M3 nylon board mounting hardware set","1",""
"MH3","M3 3.2mm","IFB01:MountingHole_3_2mm_M3","Keystone","9903","M3 nylon board mounting hardware set","1",""
"MH4","M3 3.2mm","IFB01:MountingHole_3_2mm_M3","Keystone","9903","M3 nylon board mounting hardware set","1",""
"P3","1757233","","Phoenix Contact","1757233","matching 4-position 5.08 mm screw plug for J3","1",""
"P4","1757233","","Phoenix Contact","1757233","matching 4-position 5.08 mm screw plug for J4","1",""
"P5","1757233","","Phoenix Contact","1757233","matching 4-position 5.08 mm screw plug for J5","1",""
"P6","1757233","","Phoenix Contact","1757233","matching 4-position 5.08 mm screw plug for J6","1",""
"P7","1757233","","Phoenix Contact","1757233","matching 4-position 5.08 mm screw plug for J7","1",""
"P8","1757259","","Phoenix Contact","1757259","matching 6-position 5.08 mm screw plug for J8","1",""
"P9","1757259","","Phoenix Contact","1757259","matching 6-position 5.08 mm screw plug for J9","1",""
"P10","1757314","","Phoenix Contact","1757314","matching 12-position 5.08 mm screw plug for J10","1",""
"P11","1757291","","Phoenix Contact","1757291","matching 8-position 5.08 mm screw plug for J11","1",""
"P12","1757233","","Phoenix Contact","1757233","matching 4-position 5.08 mm screw plug for J12","1",""
"R5","100k","IFB01:R_0603_1608","Yageo","RC0603FR-07100KL","100 kiloohm 1 percent GP17 pull-down","1",""
"R6","1k","IFB01:R_0603_1608","Yageo","RC0603FR-071KL","1 kiloohm GPIO output series resistors","1",""
"R7","1k","IFB01:R_0603_1608","Yageo","RC0603FR-071KL","1 kiloohm GPIO output series resistors","1",""
"R8","1k","IFB01:R_0603_1608","Yageo","RC0603FR-071KL","1 kiloohm GPIO output series resistors","1",""
"R9","1k","IFB01:R_0603_1608","Yageo","RC0603FR-071KL","1 kiloohm GPIO output series resistors","1",""
"R10","1k","IFB01:R_0603_1608","Yageo","RC0603FR-071KL","1 kiloohm GPIO output series resistors","1",""
"R11","1k","IFB01:R_0603_1608","Yageo","RC0603FR-071KL","1 kiloohm GPIO output series resistors","1",""
"R12","1k","IFB01:R_0603_1608","Yageo","RC0603FR-071KL","1 kiloohm GPIO output series resistors","1",""
"R13","1k","IFB01:R_0603_1608","Yageo","RC0603FR-071KL","1 kiloohm GPIO output series resistors","1",""
"R14","1k","IFB01:R_0603_1608","Yageo","RC0603FR-071KL","1 kiloohm GPIO output series resistors","1",""
"R15","1k","IFB01:R_0603_1608","Yageo","RC0603FR-071KL","1 kiloohm GPIO output series resistors","1",""
"R16","1k","IFB01:R_0603_1608","Yageo","RC0603FR-071KL","1 kiloohm GPIO output series resistors","1",""
"R17","1k","IFB01:R_0603_1608","Yageo","RC0603FR-071KL","1 kiloohm GPIO output series resistors","1",""
"R18","10k","IFB01:R_0603_1608","Yageo","RC0603FR-0710KL","10 kiloohm input series resistors","1",""
"R19","10k","IFB01:R_0603_1608","Yageo","RC0603FR-0710KL","10 kiloohm input series resistors","1",""
"R20","10k","IFB01:R_0603_1608","Yageo","RC0603FR-0710KL","10 kiloohm input series resistors","1",""
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
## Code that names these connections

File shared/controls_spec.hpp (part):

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inline constexpr std::uint8_t enc_right_a = 10, enc_right_b = 11;
// 24 V field loops through Phoenix PLC-RSC-24DC/21 relay couplers; the coupler
// contact closes the GPIO to 0 V (internal pull-up), so LOW = loop energised.
inline constexpr std::uint8_t in_start     = 12;  // 3SU1152-0AB40-1BA0 NO: LOW while pressed.
inline constexpr std::uint8_t in_stop_ok   = 13;  // 3SU1152-0AB20-1CA0 NC: LOW while NOT pressed (loop closed).
inline constexpr std::uint8_t in_reset     = 14;  // 3SU1152-0AB50-1BA0 NO: LOW while pressed.
inline constexpr std::uint8_t in_safety_ok = 15;  // XPSUAF13AP enabling contact 13-14: LOW while E-stop AND guard circuit closed.
inline constexpr std::uint8_t in_home_rear = 16;  // IE5338 on blade-rear carriage (PNP 24 V -> coupler): LOW at open end.
// GP17 is a TPL7407LDR input. Its shared low-side output connects all ENA- pins;
// GPIO HIGH makes ENA effective HIGH and enables all drivers. A 100 kOhm board
// pull-down keeps the channel off (all drives disabled) through reset/power loss.
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// 24 V indicators through TPL7407LDR low-side channels: HIGH = on.
inline constexpr std::uint8_t out_led_green = 22;  // in START button.
inline constexpr std::uint8_t out_led_red   = 26;  // in STOP button.
inline constexpr std::uint8_t in_home_front = 27;  // IE5338 on blade-front carriage (PNP 24 V -> coupler): LOW at open end.
inline constexpr std::uint8_t out_buzzer    = 28;  // 3SU1200-6LB10-1AA0.
// The blue LED in the RESET button is wired directly across the 24 V control
// supply ("control voltage present"); it is not a GPIO.
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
